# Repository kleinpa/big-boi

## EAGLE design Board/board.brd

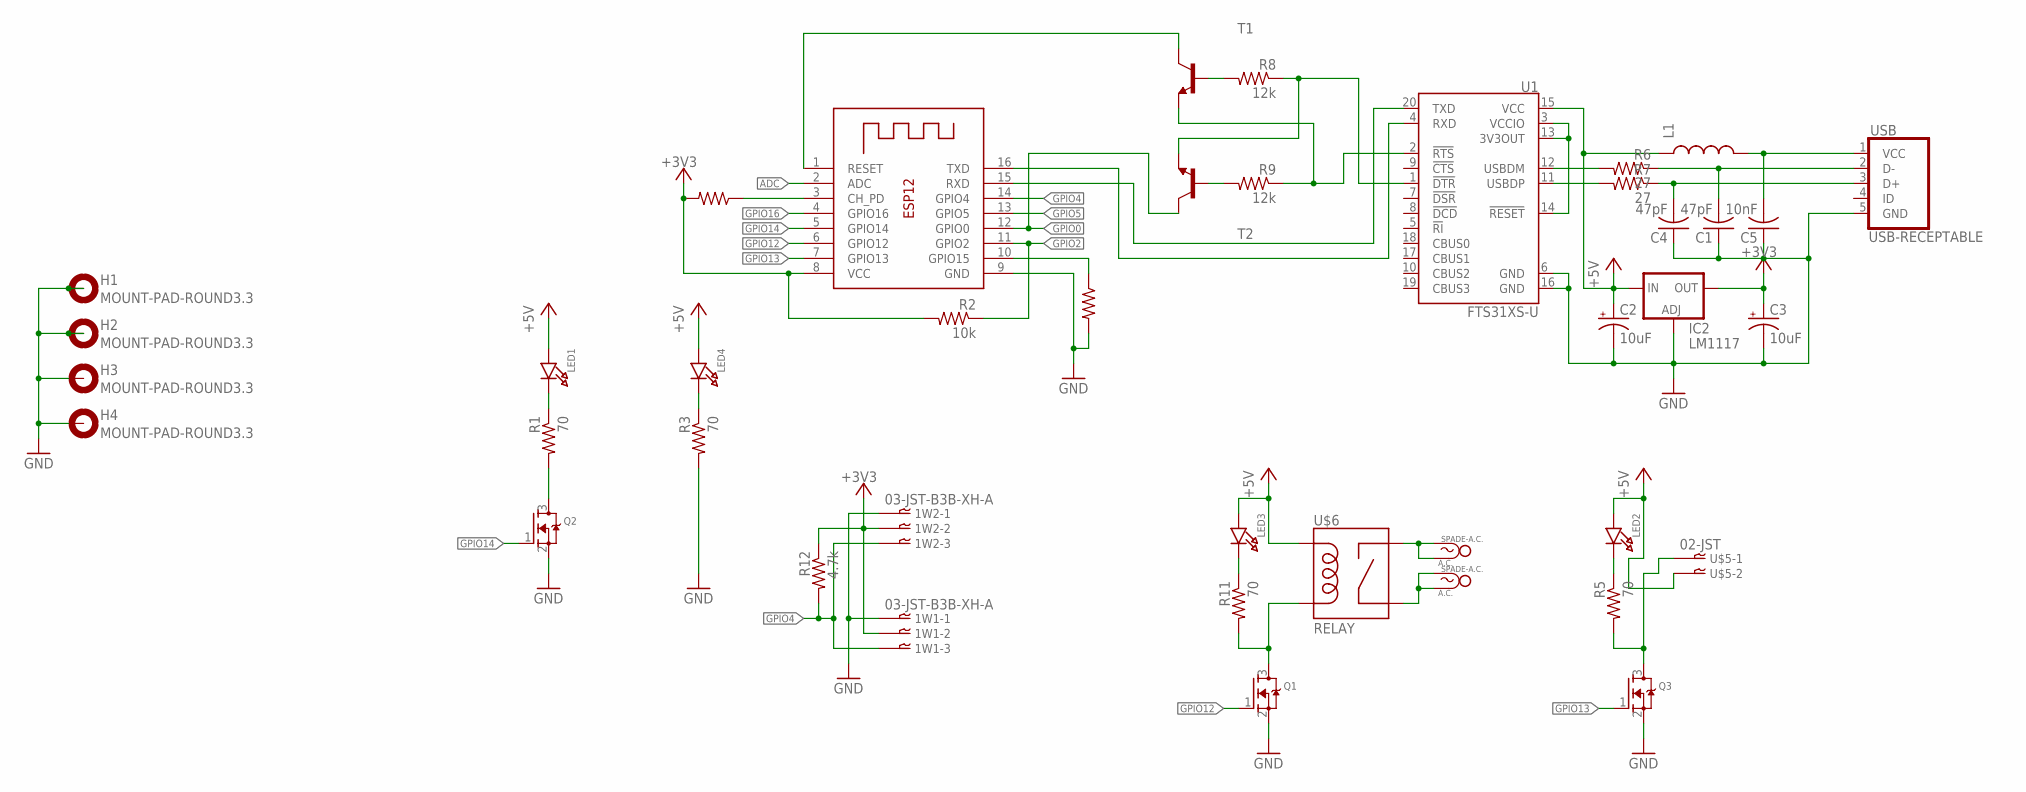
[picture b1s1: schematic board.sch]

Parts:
1W1, 1W2: 03-JST-B3B-XH-A; B3B-XH
C1, C4: 47pF; C0603
C2, C3: 10uF; 153CLV-0405
C5: 10nF; C0603
H1, H2, H3, H4: MOUNT-PAD-ROUND3.3; 3,3-PAD
IC2: LM1117; DPACK
L1: INDUCTOR0805; 0805
LED1, LED2, LED3, LED4: LED0805; CHIPLED_0805
Q1, Q2, Q3: MOSFET-NREFLOW; SOT23
R1, R3, R5, R11: 70; R0603
R2, R4, R10: 10k; R0603
R6, R7: 27; R0603
R8, R9: 12k; R0603
R12: 4.7k; R0603
T1, T2: MMBT918LT1-NPN-SOT23-BEC; SOT23-BEC
U1: FTS31XS-U; SSOP20_L
U$1, U$2: SPADE-A.C.
U$5: 02-JST; B2B-XH
U$6: RELAY; RELAY-G5NB
USB: USB-RECEPTABLE; FCI-10103594-0001LF
X1: ESP-12

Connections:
+3V3: 1W1.P$2, 1W2.P$2, C3.+, IC2.4 (OUT), R2.2, R4.2, R12.1, X1.8 (VCC)
+5V: C2.+, IC2.3 (IN), L1.1, LED1.A, LED2.A, LED3.A, LED4.A, U1.15 (VCC), U$5.P$2, U$6.1 (COIL1)
ADC: X1.2 (ADC)
GND: 1W1.P$1, 1W2.P$1, C1.1, C2.-, C3.-, C4.1, C5.1, H1.B3,3, H2.B3,3, H3.B3,3, H4.B3,3, IC2.1 (ADJ), Q1.2 (S), Q2.2 (S), Q3.2 (S), R3.2, R10.2, U1.6 (GND), U1.16 (GND), USB.5 (GND), X1.9 (GND)
GND1: Q3.3 (D), R5.2, U$5.P$1
GND2: Q1.3 (D), R11.2, U$6.4 (COIL2)
GND3: Q2.3 (D), R1.2
GPIO0: T2.C, X1.12 (GPIO0)
GPIO2: R2.1, X1.11 (GPIO2)
GPIO4: 1W1.P$3, 1W2.P$3, R12.2, X1.14 (GPIO4)
GPIO5: X1.13 (GPIO5)
GPIO12: Q1.1 (G), X1.6 (GPIO12)
GPIO13: Q3.1 (G), X1.7 (GPIO13)
GPIO14: Q2.1 (G), X1.5 (GPIO14)
GPIO15: R10.1, X1.10 (GPIO15)
GPIO16: X1.4 (GPIO16)
unnamed: R4.1, X1.3 (CH_PD)
unnamed: C4.2, R7.1, USB.3 (D+)
unnamed: R7.2, U1.11 (USBDP)
unnamed: LED4.C, R3.1
unnamed: U$2.P$1, U$2.P$2, U$6.3 (NO)
unnamed: U$1.P$1, U$1.P$2, U$6.2 (MAIN)
unnamed: C5.2, L1.2, USB.1 (VCC)
unnamed: LED3.C, R11.1
unnamed: R6.2, U1.12 (USBDM)
unnamed: LED2.C, R5.1
unnamed: LED1.C, R1.1
unnamed: C1.2, R6.1, USB.2 (D-)
unnamed: R8.1, T2.E, U1.1 (!DTR)
unnamed: R9.1, T1.E, U1.2 (!RTS)
unnamed: R8.2, T1.B
unnamed: R9.2, T2.B
unnamed: U1.3 (VCCIO), U1.13 (3V3OUT), U1.14 (!RESET)
RST: T1.C, X1.1 (RESET)
RXI: U1.20 (TXD), X1.15 (RXD)
TXO: U1.4 (RXD), X1.16 (TXD)

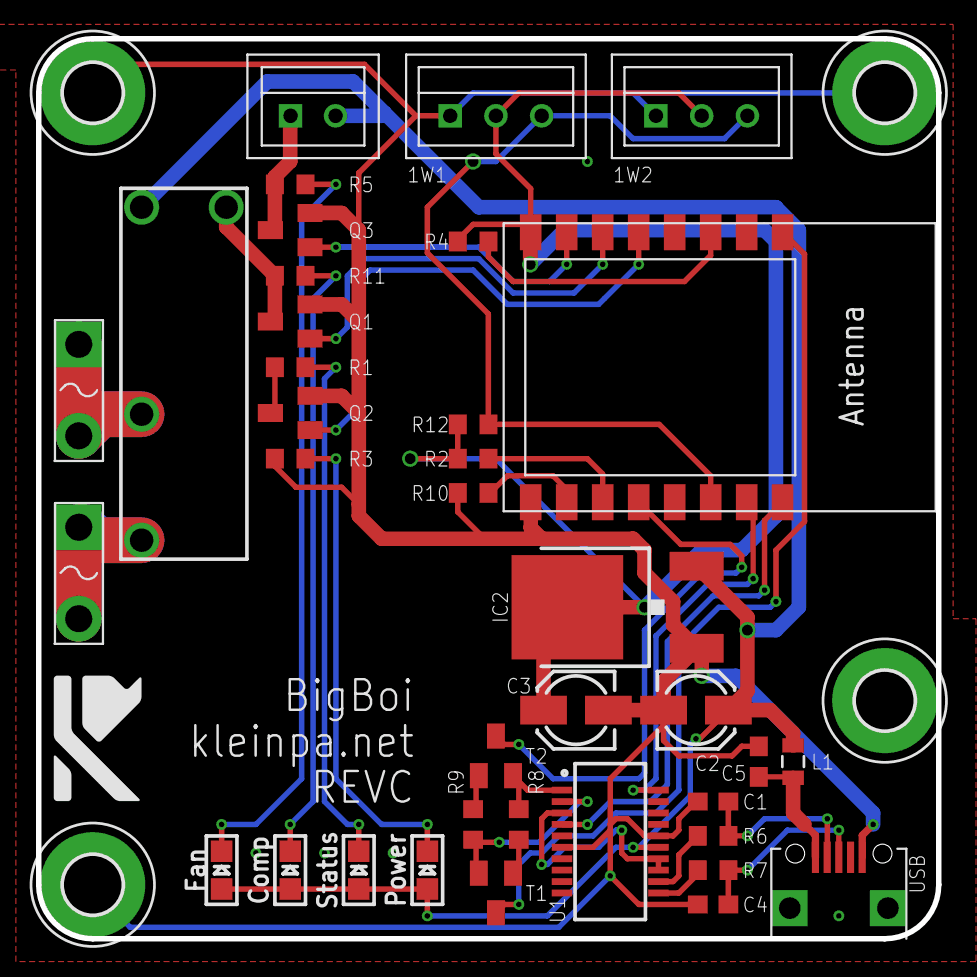
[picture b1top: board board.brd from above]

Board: 2 copper layers, 50.0 x 50.0 mm, 41 parts (0 on the bottom side), 33 nets.

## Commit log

2015-08-22 Add Eagle schematic
2015-08-22 Add esp8266-ardunio firmware
2015-08-22 Log setpoint and epsilon
2015-08-22 Reduce setpoint and try to recover from a bad temp reading
2015-08-22 Tidy up
2015-08-24 Set temperature for my recently brewed Altbier
2015-08-27 Don't use delay() for timing
2015-09-04 Add web server for controlling setpoint
2015-10-04 Remove hardcoded IP address in web page
2015-10-05 Persist state
2015-10-06 Add script to generate website
2015-10-08 Add angular web UI
    Run the compile.py to generate the header
2015-10-09 Generate byte arrays instead of strings
2016-07-17 Fix errors from REVB build
2017-08-03 Use PlatformIO
2017-08-03 Add simple thermometer

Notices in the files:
parts and their libraries:
SparkFun-DigitalIC: Licensing: Creative Commons ShareAlike 4.0 International - https://creativecommons.org/licenses/by-sa/4.0
